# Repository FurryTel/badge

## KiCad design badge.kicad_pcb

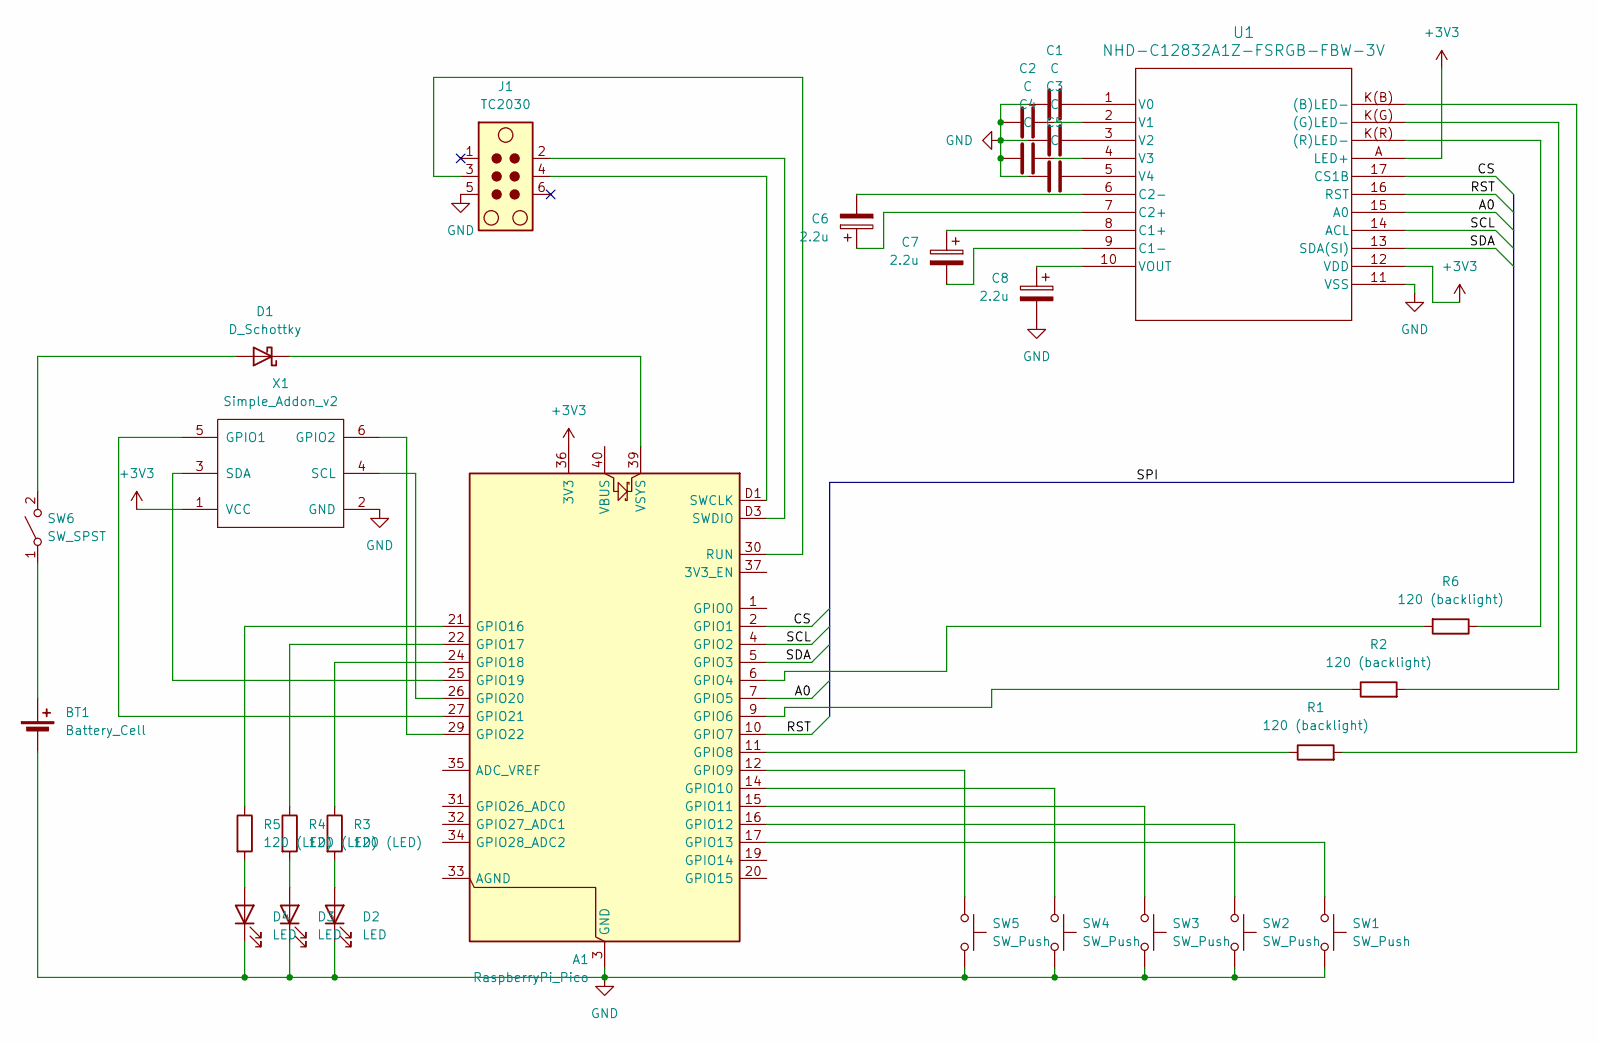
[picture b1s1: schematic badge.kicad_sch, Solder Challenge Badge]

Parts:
A1: RaspberryPi_Pico; RaspberryPi_Pico_SMD_HandSolder
BT1: Battery_Cell; BatteryHolder_Keystone_2479_3xAAA_NoHole
C1, C2, C3, C4, C5: C; C_Disc_D5.0mm_W2.5mm_P5.00mm
C6, C7, C8: 2.2u; CP_Radial_D5.0mm_P2.00mm
D1: D_Schottky; D_DO-35_SOD27_P10.16mm_Horizontal
D2, D3, D4: LED; LED_D5.0mm
J1: TC2030; Paw-Connect_RevB_TC2030-IDC-NL_2x03_P1.27mm_Vertical
R1, R2, R6: 120 (backlight); R_Axial_DIN0207_L6.3mm_D2.5mm_P10.16mm_Horizontal
R3, R4, R5: 120 (LED); R_Axial_DIN0207_L6.3mm_D2.5mm_P10.16mm_Horizontal
SW1, SW2, SW3, SW4, SW5: SW_Push; SW_PUSH_6mm
SW6: SW_SPST; SW_SLW-1277744-3A-N-D
U1: NHD-C12832A1Z-FSRGB-FBW-3V; NHD-C12_NDI
X1: Simple_Addon_v2; Simple_Addon_v2-BADGE-2x3

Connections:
+3V3: A1.36 (3V3), U1.12 (VDD), U1.A (LED+), X1.1 (VCC)
/A0: A1.7 (GPIO5), U1.15 (A0)
/CS: A1.2 (GPIO1), U1.17 (CS1B)
/RST: A1.10 (GPIO7), U1.16 (RST)
/SCL: A1.4 (GPIO2), U1.14 (ACL)
/SDA: A1.5 (GPIO3), U1.13 (SDA(SI))
GND: A1.3 (GND), A1.8 (GND), A1.13 (GND), A1.18 (GND), A1.23 (GND), A1.28 (GND), A1.38 (GND), A1.D2 (GND), BT1.2 (-), C1.1, C2.1, C3.1, C4.1, C5.1, C8.2, D2.1 (K), D3.1 (K), D4.1 (K), J1.5, SW1.2, SW2.2, SW3.2, SW4.2, SW5.2, U1.11 (VSS), X1.2 (GND)
unnamed: A1.6 (GPIO4), R6.2
unnamed: A1.9 (GPIO6), R2.1
unnamed: A1.11 (GPIO8), R1.1
unnamed: A1.12 (GPIO9), SW5.1
unnamed: A1.14 (GPIO10), SW4.1
unnamed: A1.15 (GPIO11), SW3.1
unnamed: A1.16 (GPIO12), SW2.1
unnamed: A1.17 (GPIO13), SW1.1
unnamed: A1.21 (GPIO16), R5.1
unnamed: A1.22 (GPIO17), R4.1
unnamed: A1.24 (GPIO18), R3.1
unnamed: A1.25 (GPIO19), X1.3 (SDA)
unnamed: A1.26 (GPIO20), X1.4 (SCL)
unnamed: A1.27 (GPIO21), X1.5 (GPIO1)
unnamed: A1.29 (GPIO22), X1.6 (GPIO2)
unnamed: A1.30 (RUN), J1.3
unnamed: A1.D1 (SWCLK), J1.4
unnamed: A1.D3 (SWDIO), J1.2
unnamed: A1.39 (VSYS), D1.1 (K)
unnamed: BT1.1 (+), SW6.1 (A)
unnamed: D1.2 (A), SW6.2 (B)
unnamed: D2.2 (A), R3.2
unnamed: D3.2 (A), R4.2
unnamed: D4.2 (A), R5.2
unnamed: R1.2, U1.K(B) ((B)LED-)
unnamed: R2.2, U1.K(G) ((G)LED-)
unnamed: R6.1, U1.K(R) ((R)LED-)
unnamed: C7.1, U1.8 (C1+)
unnamed: C7.2, U1.9 (C1-)
unnamed: C6.1, U1.7 (C2+)
unnamed: C6.2, U1.6 (C2-)
unnamed: C1.2, U1.1 (V0)
unnamed: C2.2, U1.2 (V1)
unnamed: C3.2, U1.3 (V2)
unnamed: C4.2, U1.4 (V3)
unnamed: C5.2, U1.5 (V4)
unnamed: C8.1, U1.10 (VOUT)

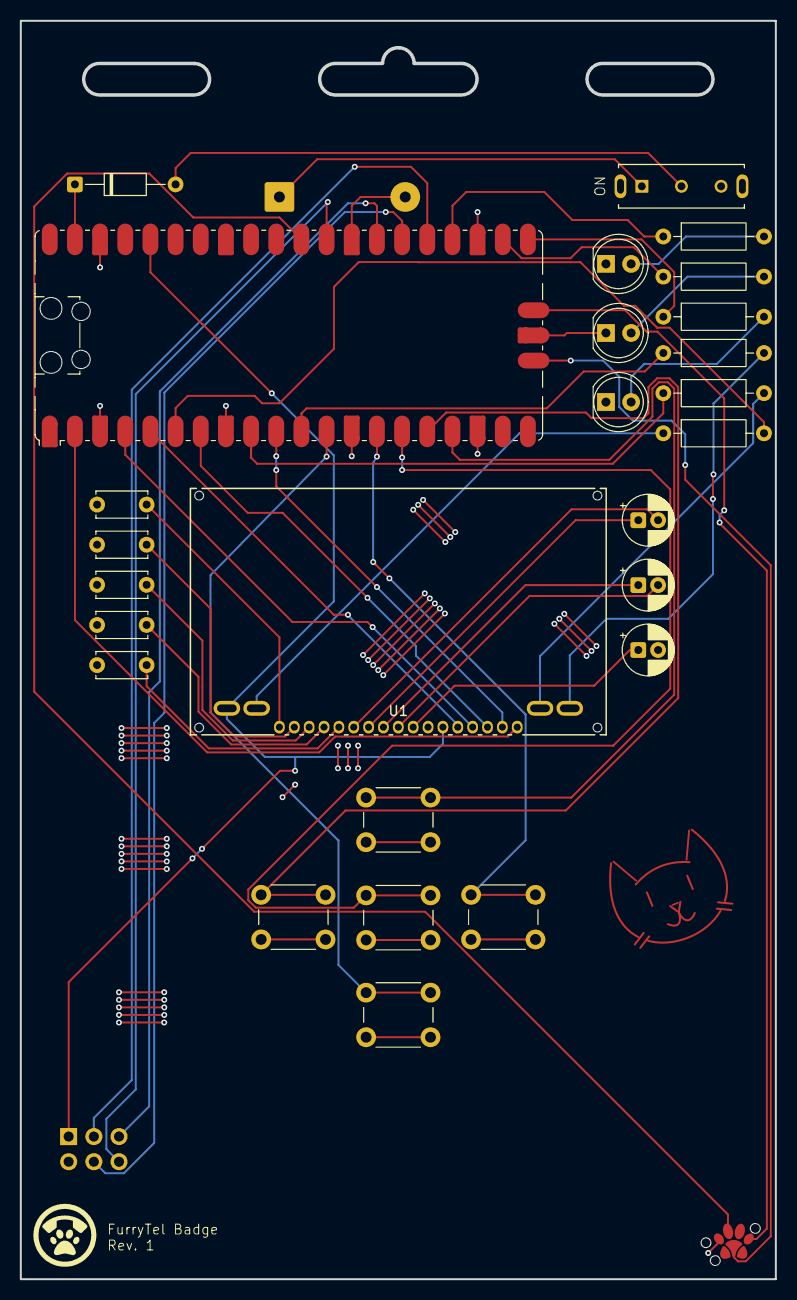
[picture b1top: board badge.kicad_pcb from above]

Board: 2 copper layers, 76.2 x 127.0 mm, 31 parts (1 on the bottom side), 44 nets.

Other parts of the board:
FTLOGO: Logo
LANYARD: Lanyard_Alt
